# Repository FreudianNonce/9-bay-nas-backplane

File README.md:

# DIY 9-Bay NAS Backplane

> A simple and compact 9-Bay Backplance for a compact NAS application.

## Overview

This backplane is designed for connectivity for up to 8 SATA 3.0 storage drives connected to a PCIE HBA, as well as one slot for a SATA 3.0 boot drive connected to a motherboard SATA header. This board was specifically designed to be used in a Fractal Terra with an HDPLEX 250w GaN PSU, but should work for any small form factor NAS.

## Specifications

Dimensions: 115mmx58mm
Power Connector: 4-pin peripheral
Supply Voltage: 5v
Hot Swap: Hardware Supported (HBA must also support)

## Project Status

We've reached version 1.2 of this project. It took longer than I hoped, but I've built and tested this version and am currently running it in my NAS.

## Changes

Changes since version 1.0 include the following

- updated power connector to 4-pin peripheral (goodbye screw terminal)
- updated bulk capacitors to an appropriate size
- removed the 12v rail (only 5v is needed for SSDs)
- added full ground plane
- fixed SATA Data differential pair balancing
- added large isolation zone

## Making

Actually making one of these backplanes is very tedious. I can only recommend this if you have fine soldering skills.

If you do decide to make this, this is how I assembeled it.

- solder the SMD capacitors and resistors first. It is recommended that you use a solder reflow station. 
- for SATA interfaces, start on the end of the board that is furthest away from the power through holes
- use two 22-pin SATA connectors (one on J901 and one on J101, for balance), solder J901
- flip the board over and use three 7-pin SATA connectors (one on J902, J102, and the edge of the board where its falling over), solder J902
- flip the board over and repeat for all slots in descending order.
- once all the slots are soldered, solder the bulk capacitors, and 4-pin power. order doesnt matter here

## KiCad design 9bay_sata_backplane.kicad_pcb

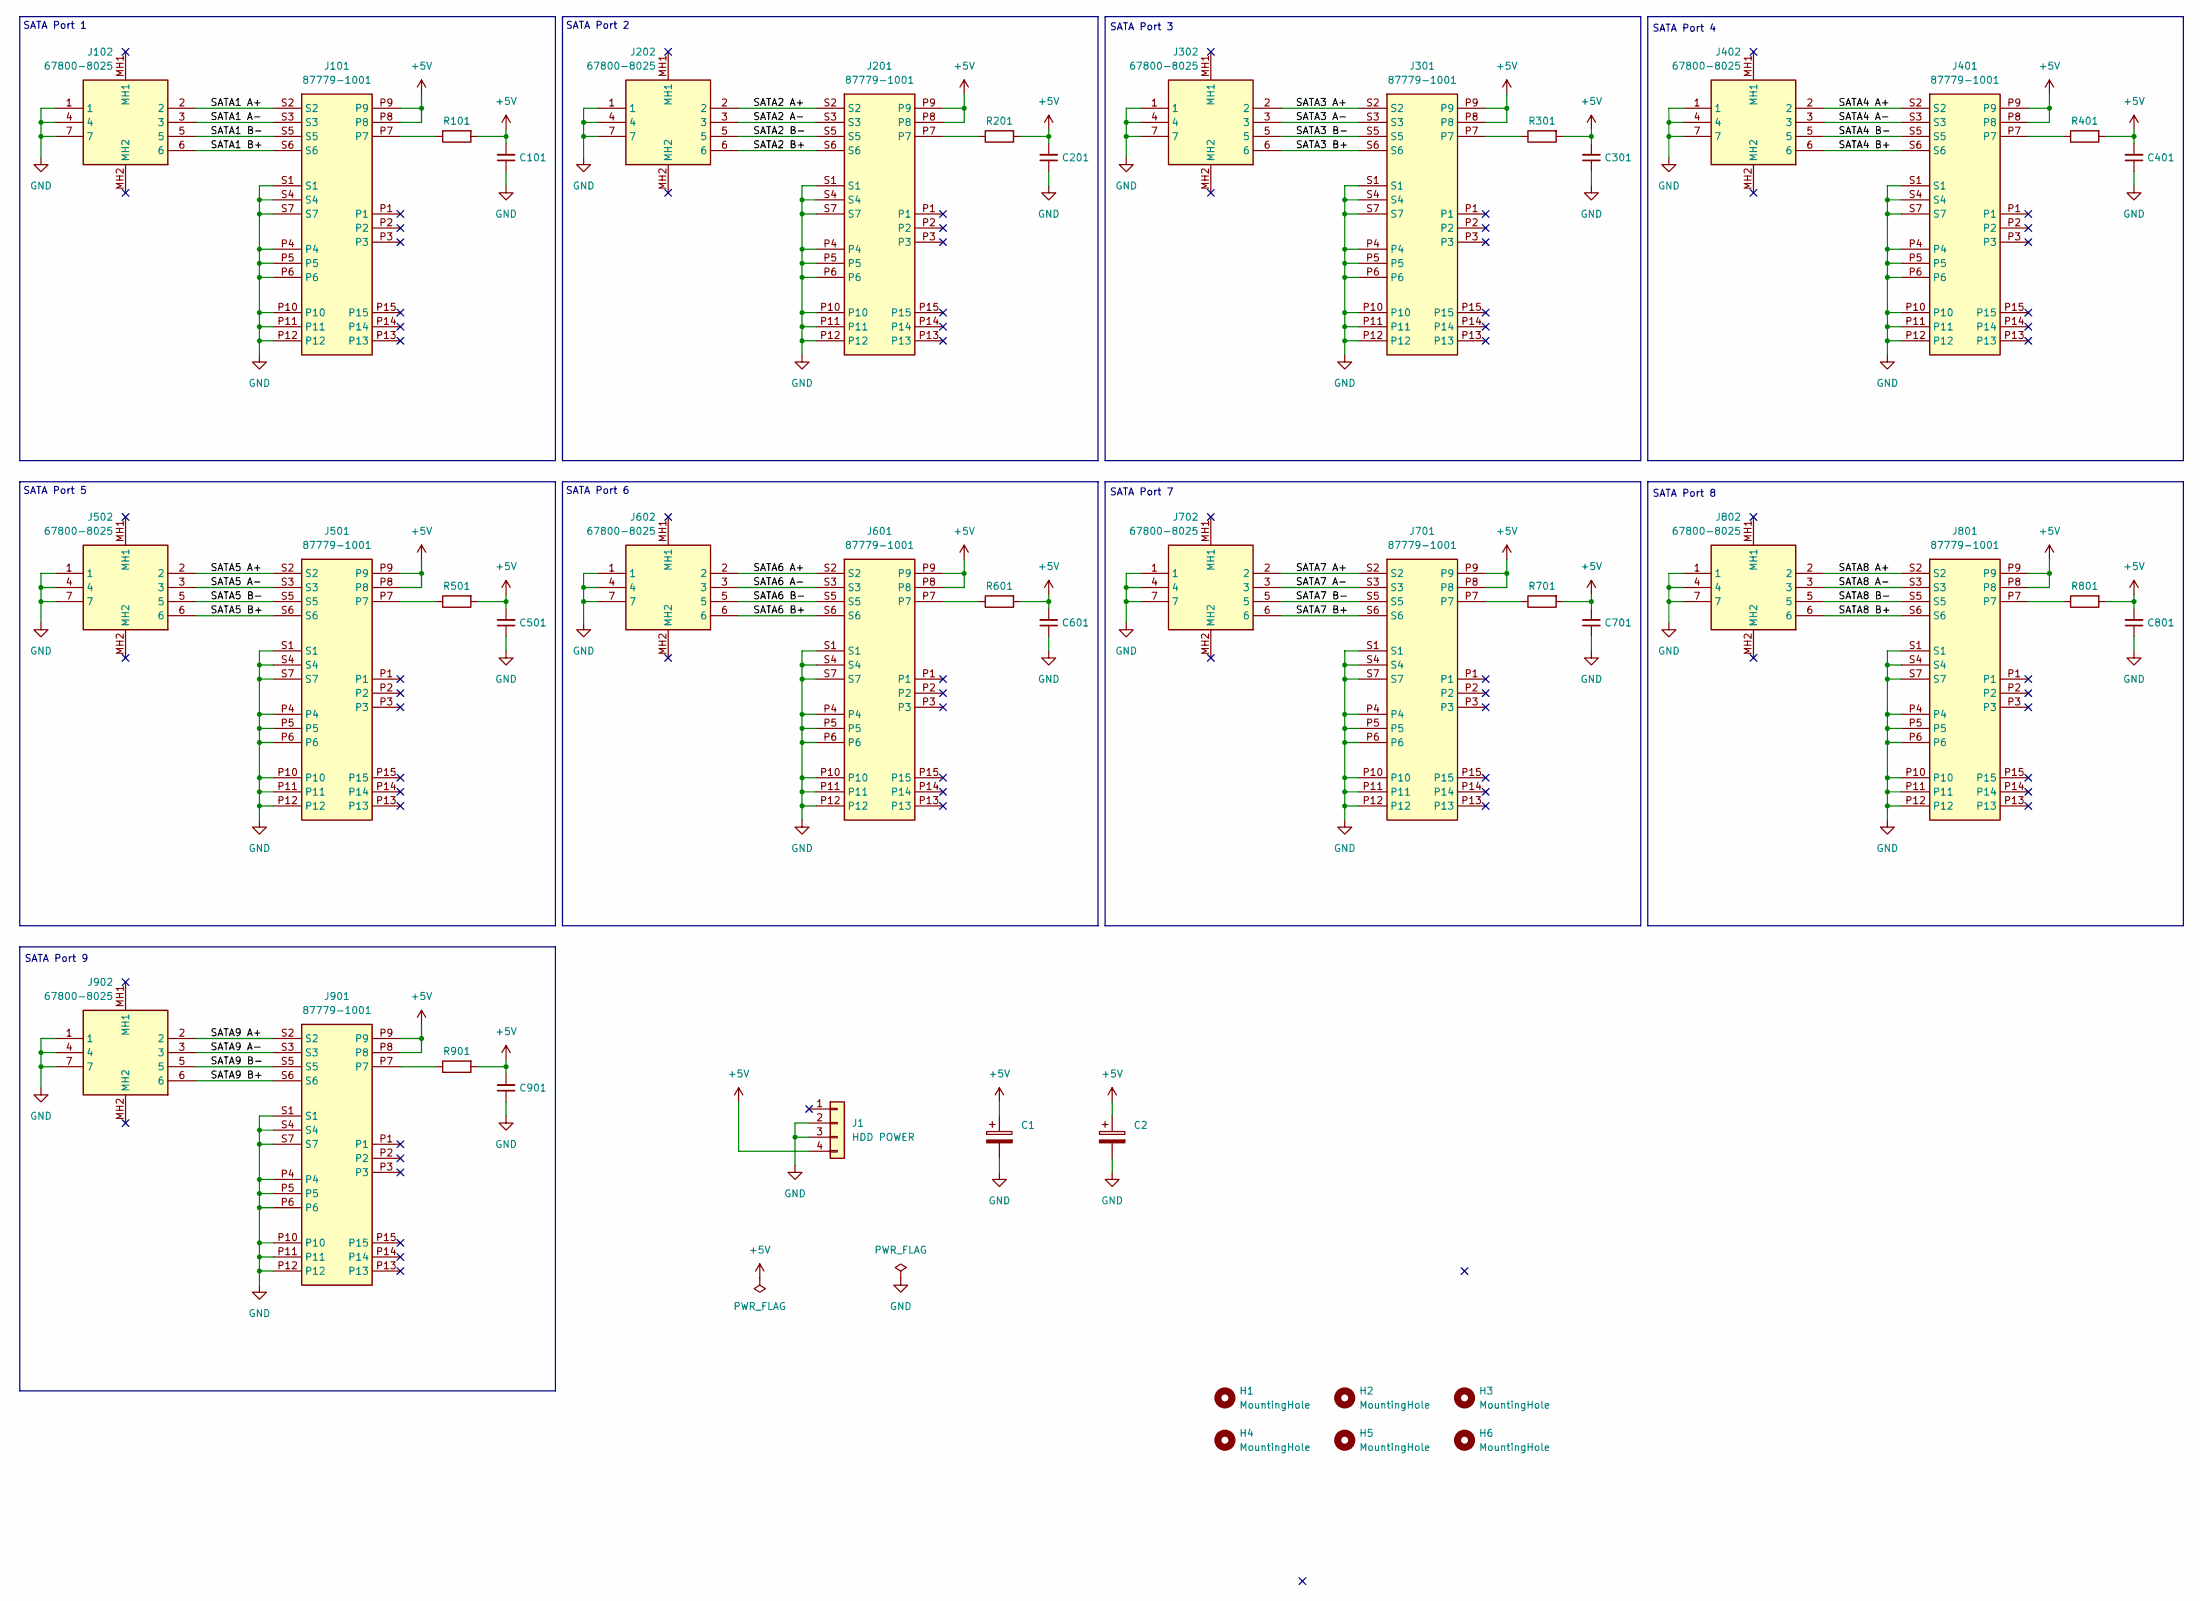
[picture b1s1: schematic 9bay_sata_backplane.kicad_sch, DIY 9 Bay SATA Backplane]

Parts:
C1, C2: 25v 560uf; CP_Radial_D10.0mm_P5.00mm
C101, C201, C301, C401, C501, C601, C701, C801, C901: 35v 10uf; C_1206_3216Metric
H1, H2, H3, H4, H5, H6: MountingHole; MountingHole_3mm
J1: HDD POWER; TE_MATE-N-LOK_350211-1_1x04_P5.08mm_Vertical
J101, J201, J301, J401, J501, J601, J701, J801, J901: 87779-1001; 877791001; Manufacturer_Part_Number 87779-1001; Mouser Part Number 538-87779-1001
J102, J202, J302, J402, J502, J602, J702, J802, J902: 67800-8025; 678008025; Manufacturer_Part_Number 67800-8025; Mouser Part Number 538-67800-8025
R101, R201, R301, R401, R501, R601, R701, R801, R901: 22ohm; R_1206_3216Metric

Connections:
+5V: C1.1, C2.1, C101.2, C201.2, C301.2, C401.2, C501.2, C601.2, C701.2, C801.2, C901.2, J1.4, J101.P8, J101.P9, J201.P8, J201.P9, J301.P8, J301.P9, J401.P8, J401.P9, J501.P8, J501.P9, J601.P8, J601.P9, J701.P8, J701.P9, J801.P8, J801.P9, J901.P8, J901.P9, R101.2, R201.2, R301.2, R401.2, R501.2, R601.2, R701.2, R801.2, R901.2
/SATA1 A+: J101.S2, J102.2
/SATA1 A-: J101.S3, J102.3
/SATA1 B+: J101.S6, J102.6
/SATA1 B-: J101.S5, J102.5
/SATA2 A+: J201.S2, J202.2
/SATA2 A-: J201.S3, J202.3
/SATA2 B+: J201.S6, J202.6
/SATA2 B-: J201.S5, J202.5
/SATA3 A+: J301.S2, J302.2
/SATA3 A-: J301.S3, J302.3
/SATA3 B+: J301.S6, J302.6
/SATA3 B-: J301.S5, J302.5
/SATA4 A+: J401.S2, J402.2
/SATA4 A-: J401.S3, J402.3
/SATA4 B+: J401.S6, J402.6
/SATA4 B-: J401.S5, J402.5
/SATA5 A+: J501.S2, J502.2
/SATA5 A-: J501.S3, J502.3
/SATA5 B+: J501.S6, J502.6
/SATA5 B-: J501.S5, J502.5
/SATA6 A+: J601.S2, J602.2
/SATA6 A-: J601.S3, J602.3
/SATA6 B+: J601.S6, J602.6
/SATA6 B-: J601.S5, J602.5
/SATA7 A+: J701.S2, J702.2
/SATA7 A-: J701.S3, J702.3
/SATA7 B+: J701.S6, J702.6
/SATA7 B-: J701.S5, J702.5
/SATA8 A+: J801.S2, J802.2
/SATA8 A-: J801.S3, J802.3
/SATA8 B+: J801.S6, J802.6
/SATA8 B-: J801.S5, J802.5
/SATA9 A+: J901.S2, J902.2
/SATA9 A-: J901.S3, J902.3
/SATA9 B+: J901.S6, J902.6
/SATA9 B-: J901.S5, J902.5
GND: C1.2, C2.2, C101.1, C201.1, C301.1, C401.1, C501.1, C601.1, C701.1, C801.1, C901.1, J1.2, J1.3, J101.P4, J101.P5, J101.P6, J101.P10, J101.P11, J101.P12, J101.S1, J101.S4, J101.S7, J102.1, J102.4, J102.7, J201.P4, J201.P5, J201.P6, J201.P10, J201.P11, J201.P12, J201.S1, J201.S4, J201.S7, J202.1, J202.4, J202.7, J301.P4, J301.P5, J301.P6, J301.P10, J301.P11, J301.P12, J301.S1, J301.S4, J301.S7, J302.1, J302.4, J302.7, J401.P4, J401.P5, J401.P6, J401.P10, J401.P11, J401.P12, J401.S1, J401.S4, J401.S7, J402.1, J402.4, J402.7, J501.P4, J501.P5, J501.P6, J501.P10, J501.P11, J501.P12, J501.S1, J501.S4, J501.S7, J502.1, J502.4, J502.7, J601.P4, J601.P5, J601.P6, J601.P10, J601.P11, J601.P12, J601.S1, J601.S4, J601.S7, J602.1, J602.4, J602.7, J701.P4, J701.P5, J701.P6, J701.P10, J701.P11, J701.P12, J701.S1, J701.S4, J701.S7, J702.1, J702.4, J702.7, J801.P4, J801.P5, J801.P6, J801.P10, J801.P11, J801.P12, J801.S1, J801.S4, J801.S7, J802.1, J802.4, J802.7, J901.P4, J901.P5, J901.P6, J901.P10, J901.P11, J901.P12, J901.S1, J901.S4, J901.S7, J902.1, J902.4, J902.7
unnamed: J101.P7, R101.1
unnamed: J201.P7, R201.1
unnamed: J301.P7, R301.1
unnamed: J401.P7, R401.1
unnamed: J501.P7, R501.1
unnamed: J601.P7, R601.1
unnamed: J701.P7, R701.1
unnamed: J801.P7, R801.1
unnamed: J901.P7, R901.1

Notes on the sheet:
SATA Port 9
SATA Port 8
SATA Port 6
SATA Port 7
SATA Port 2
SATA Port 5
SATA Port 4
SATA Port 3
SATA Port 1

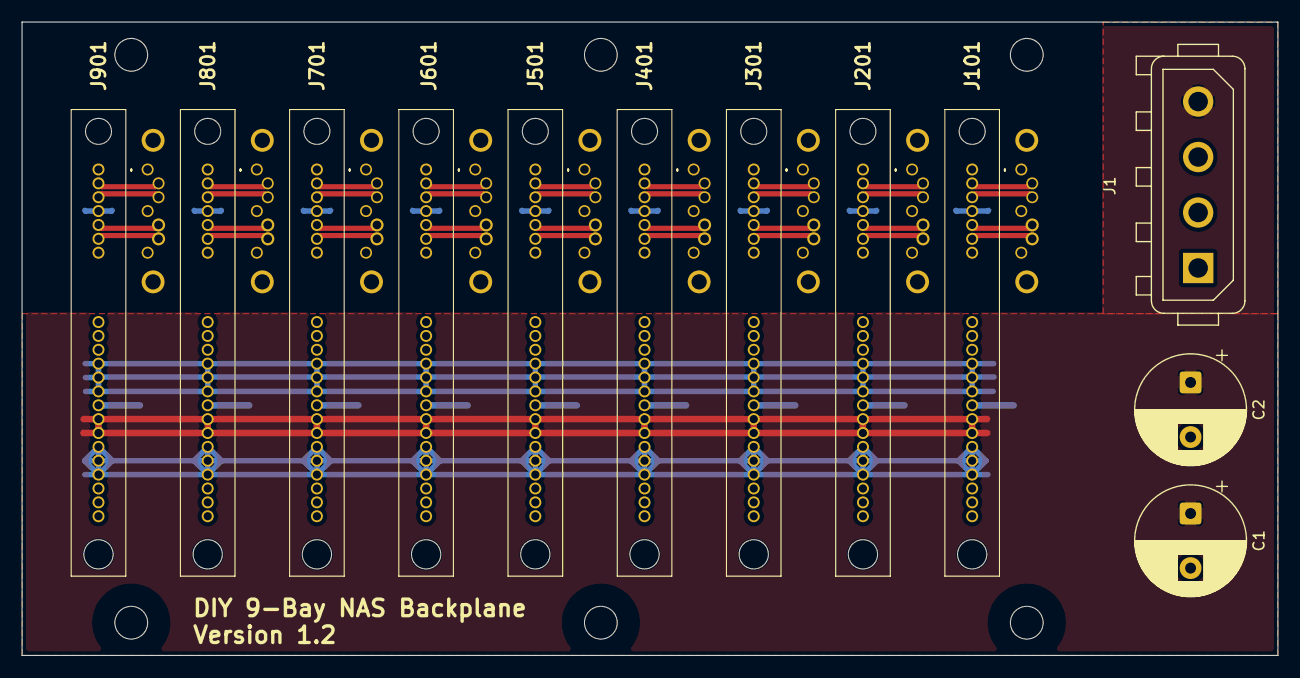
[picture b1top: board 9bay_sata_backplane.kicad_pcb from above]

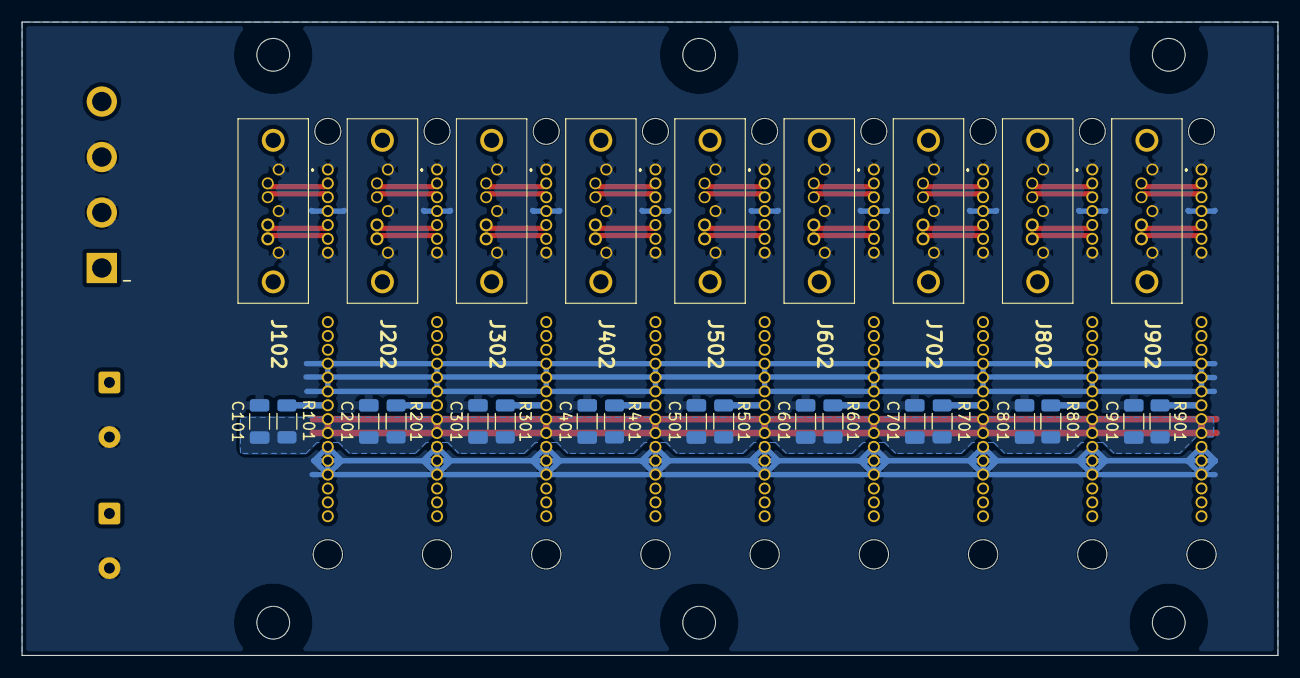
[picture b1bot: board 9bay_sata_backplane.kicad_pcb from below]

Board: 2 copper layers, 115.0 x 58.0 mm, 45 parts (27 on the bottom side), 47 nets.

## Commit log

2025-11-16 Create LICENSE
2025-11-16 added drive cage 3d print
2026-06-30 DIY 9-Bay SATA Backplane v1.2
2026-06-30 Update LICENSE
